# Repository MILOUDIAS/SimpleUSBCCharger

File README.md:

# SimpleUSBCCharger
Very Basic USB C Charger designed in kicad

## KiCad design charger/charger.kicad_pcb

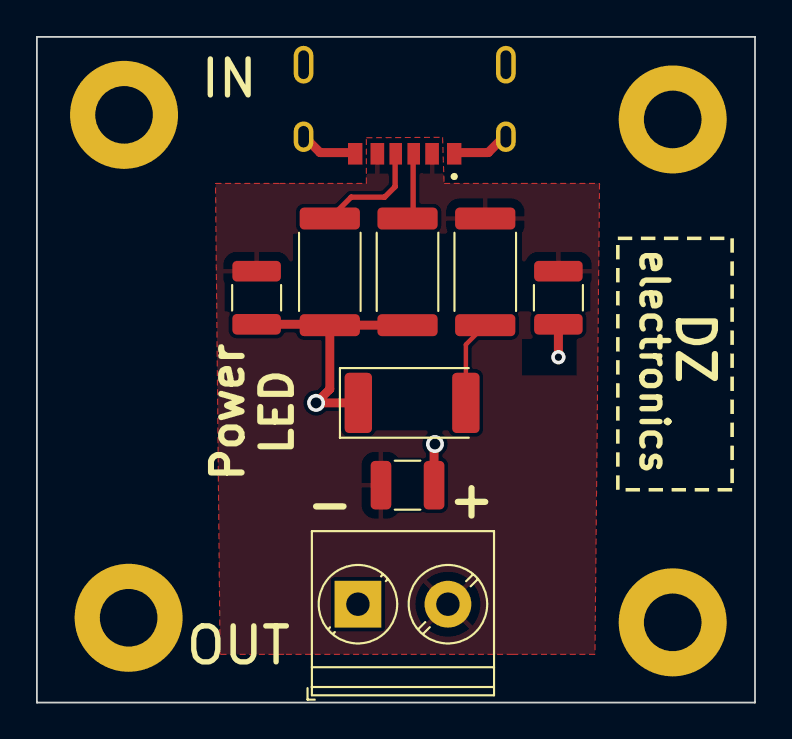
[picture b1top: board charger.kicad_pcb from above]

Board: 2 copper layers, 39.9 x 37.0 mm, 13 parts (0 on the bottom side), 5 nets.

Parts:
C1, C2, C3: 100n; C_1210_3225Metric
D1: LED; LED_2512_6332Metric_Pad1.52x3.35mm_HandSolder
H1, H2, H3, H4: MountingHole_M3_3.2mm_Pad; MountingHole_3.2mm_Pad
J2: USB4515-GF-A_REVA; USBC_PD_6PINS
J3: Screw_Terminal_2_P5.00mm; TerminalBlock_Phoenix_PT-1,5-2-5.0-H_1x02_P5.00mm_Horizontal
R1, R2: 5.1k; R_2512_6332Metric
R3: 220; R_2512_6332Metric

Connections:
+5V: C1.1, C2.1, C3.1, J2.A9 (VBUS), J2.B9 (VBUS), J3.2, R3.1
/CC1: J2.A5 (CC1), R2.1
/CC2: J2.B5 (CC2), R1.1
/LED: D1.2 (A), R3.2
GND: C1.2, C2.2, C3.2, D1.1 (K), H1.1, H2.1, H3.1, H4.1, J2.A12 (GND), J2.B12 (GND), J2.S1 (SHIELD), J2.S2 (SHIELD), J2.S3 (SHIELD), J2.S4 (SHIELD), J3.1, R1.2, R2.2

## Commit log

2024-03-12 added all folders
2024-03-30 added usb-c footprint
2024-03-30 added power/ground planes
2024-03-31 fixed segments edge.cuts error and changed the pcb a little bit
2024-04-16 ready for testing
